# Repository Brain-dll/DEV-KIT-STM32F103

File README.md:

# dev_kit_f103
The project will be developed for designing new usable development kit with ARM cortex -M3 based STM32F103C8

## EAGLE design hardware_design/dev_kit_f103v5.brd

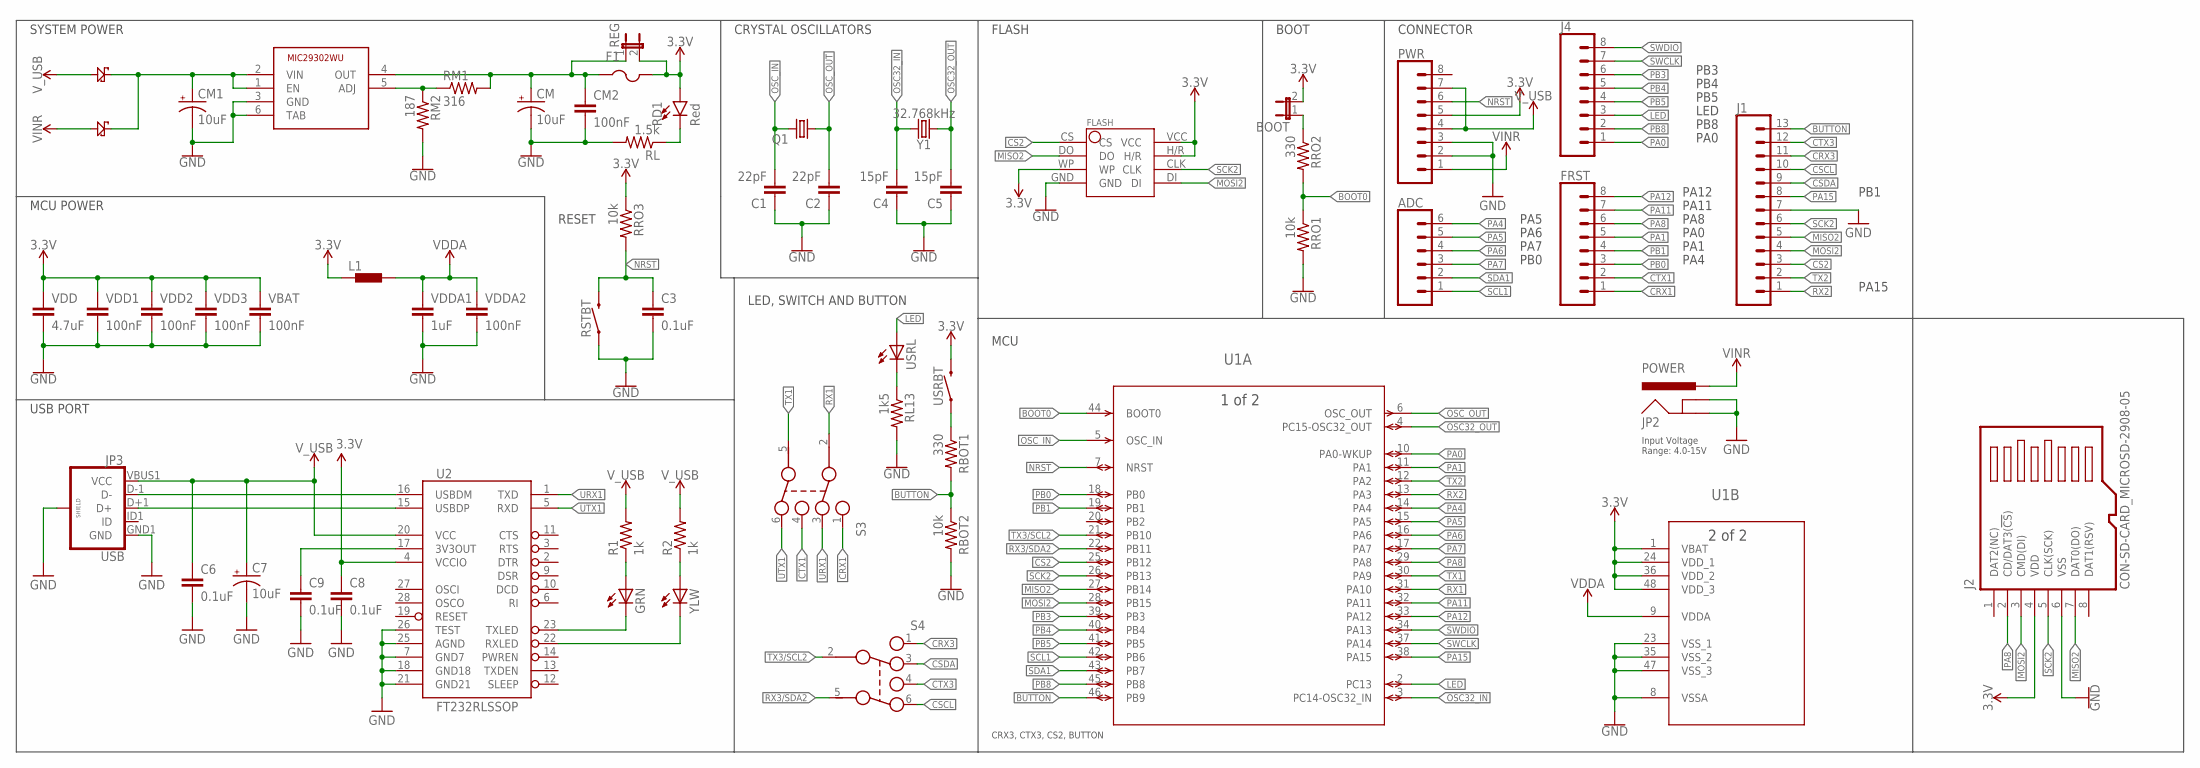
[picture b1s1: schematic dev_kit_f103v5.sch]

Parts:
ADC: CONN_06SILK_FEMALE_PTH; 1X06
BOOT: JP1E; JP1
C1, C2: 22pF; 0603
C3: 0.1uF; 0603
C4, C5: 15pF; 0603
C6, C8, C9: 0.1uF; 0402-CAP
C7: 10uF; EIA3216
CM, CM1: 10uF; EIA3528
CM2: 100nF; 0603
D1, D2: 3ASCHOOTKY
F1: PTCFUSE-1812; 1812
FLASH: W25Q64
FRST: CONN_08"; 1X08
GRN: LEDCHIP-LED0603; CHIP-LED0603
IC1: MIC29302WU; TO263-5
J1: CONN_13; 1X13
J2: CON-SD-CARD_MICROSD-2908-05; CON-SD-CARD_2908-05
J4: CONN_08"; 1X08
JP2: POWER; POWER_JACK_PTH_LOCK
JP3: USB; USB-B-MICRO-SMD_V03
L1: BLM15HB221SN1; 0402
PWR: CONN_08"; 1X08
Q1: CRYSTALHC49S; HC49/S
R1, R2: 1k; 0402-RES
RBOT1: 330; 0603-RES
RBOT2: 10k; 0603-RES
RD1: Red; LED-0603
REG: JP1E; JP1
RL: 1.5k; 0603-RES
RL13: 1k5; 0603-RES
RM1: 316; 0603-RES
RM2: 187; 0603-RES
RRO1, RRO3: 10k; 0603-RES
RRO2: 330; 0603-RES
RSTBT: MOMENTARY-SWITCH-SPST-SMD-6.0X3.5MM; TACTILE_SWITCH_SMD_6.0X3.5MM
S3, S4: 452403012014
U1: STM32F103C8T6; LQFP48-7X7MM
U2: FT232RLSSOP; SSOP28DB
USRBT: MOMENTARY-SWITCH-SPST-SMD-6.0X3.5MM; TACTILE_SWITCH_SMD_6.0X3.5MM
USRL: LEDCHIP-LED0603; CHIP-LED0603
VBAT: 100nF; 0603
VDD: 4.7uF; 0603
VDD1, VDD2, VDD3: 100nF; 0603
VDDA1: 1uF; 0603
VDDA2: 100nF; 0603
Y1: 32.768kHz; CRYSTAL-PTH-2X6-CYL-KIT
YLW: LEDCHIP-LED0603; CHIP-LED0603

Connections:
3.3V: BOOT.2, F1.2, FLASH.H/R, FLASH.VCC, FLASH.WP, J2.4 (VDD), L1.1, PWR.5, RD1.A, REG.2, RRO3.1, U1.1 (VBAT), U1.24 (VDD_1), U1.36 (VDD_2), U1.48 (VDD_3), USRBT.2, VBAT.1, VDD.1, VDD1.1, VDD2.1, VDD3.1
BOOT0: RRO1.1, RRO2.2, U1.44 (BOOT0)
BUTTON: J1.13, RBOT1.2, RBOT2.1, U1.46 (PB9)
CRX1: FRST.1, S3.1
CRX3: J1.11, S4.1
CS2: FLASH.CS, J1.3, U1.25 (PB12)
CSCL: J1.10, S4.6
CSDA: J1.9, S4.3
CTX1: FRST.2, S3.4
CTX3: J1.12, S4.4
GND: C1.1, C2.1, C3.2, C4.1, C5.1, C6.2, C7.C (-), C8.2, C9.2, CM.C (-), CM1.C (-), CM2.2, FLASH.GND, IC1.3 (GND), IC1.6 (TAB), J1.7, J2.6 (VSS), JP2.GND, JP2.GNDBREAK, JP3.GND1 (GND), JP3.SHIELD1 (SHIELD), JP3.SHIELD2 (SHIELD), JP3.SHIELD3 (SHIELD), PWR.2, PWR.3, RBOT2.2, RL.2, RL13.2, RM2.2, RRO1.2, RSTBT.1, U1.8 (VSSA), U1.23 (VSS_1), U1.35 (VSS_2), U1.47 (VSS_3), U2.7 (GND7), U2.18 (GND18), U2.21 (GND21), U2.25 (AGND), U2.26 (TEST), VBAT.2, VDD.2, VDD1.2, VDD2.2, VDD3.2, VDDA1.2, VDDA2.2
LED: J4.3, U1.2 (PC13), USRL.A
MISO2: FLASH.DO, J1.5, J2.7 (DAT0(DO)), U1.27 (PB14)
MOSI2: FLASH.DI, J1.4, J2.3 (CMD(DI)), U1.28 (PB15)
unnamed: CM1.A (+), D1.OUT, D2.OUT, IC1.1 (EN), IC1.2 (VIN)
unnamed: CM.A (+), CM2.1, F1.1, IC1.4 (OUT), REG.1, RM1.2
unnamed: BOOT.1, RRO2.1
unnamed: RL13.1, USRL.C
unnamed: RBOT1.1, USRBT.1
unnamed: GRN.A, R1.1
unnamed: R2.1, YLW.A
unnamed: C9.1, U2.17 (3V3OUT)
unnamed: IC1.5 (ADJ), RM1.1, RM2.1
unnamed: RD1.C, RL.1
NRST: C3.1, PWR.6, RRO3.2, RSTBT.2, U1.7 (NRST)
OSC32_IN: C4.2, U1.3 (PC14-OSC32_IN), Y1.2
OSC32_OUT: C5.2, U1.4 (PC15-OSC32_OUT), Y1.1
OSC_IN: C1.2, Q1.2, U1.5 (OSC_IN)
OSC_OUT: C2.2, Q1.1, U1.6 (OSC_OUT)
PA0: J4.1, U1.10 (PA0-WKUP)
PA1: FRST.5, U1.11 (PA1)
PA4: ADC.6, U1.14 (PA4)
PA5: ADC.5, U1.15 (PA5)
PA6: ADC.4, U1.16 (PA6)
PA7: ADC.3, U1.17 (PA7)
PA8: FRST.6, J2.2 (CD/DAT3(!CS!)), U1.29 (PA8)
PA11: FRST.7, U1.32 (PA11)
PA12: FRST.8, U1.33 (PA12)
PA15: J1.8, U1.38 (PA15)
PB0: FRST.3, U1.18 (PB0)
PB1: FRST.4, U1.19 (PB1)
PB3: J4.6, U1.39 (PB3)
PB4: J4.5, U1.40 (PB4)
PB5: J4.4, U1.41 (PB5)
PB8: J4.2, U1.45 (PB8)
RX1: S3.2, U1.31 (PA10)
RX2: J1.1, U1.13 (PA3)
RX3/SDA2: S4.5, U1.22 (PB11)
RXLED: U2.22 (RXLED), YLW.C
SCK2: FLASH.CLK, J1.6, J2.5 (CLK(SCK)), U1.26 (PB13)
SCL1: ADC.1, U1.42 (PB6)
SDA1: ADC.2, U1.43 (PB7)
SWCLK: J4.7, U1.37 (PA14)
SWDIO: J4.8, U1.34 (PA13)
TX1: S3.5, U1.30 (PA9)
TX2: J1.2, U1.12 (PA2)
TX3/SCL2: S4.2, U1.21 (PB10)
TXLED: GRN.C, U2.23 (TXLED)
URX1: S3.3, U2.1 (TXD)
USB_D+: JP3.D+1 (D+), U2.15 (USBDP)
USB_D-: JP3.D-1 (D-), U2.16 (USBDM)
UTX1: S3.6, U2.5 (RXD)
VCC: C8.1, U2.4 (VCCIO)
VDDA: L1.2, U1.9 (VDDA), VDDA1.1, VDDA2.1
VIN: D2.IN, JP2.PWR, PWR.1
V_USB: C6.1, C7.A (+), D1.IN, JP3.VBUS1 (VCC), PWR.4, PWR.7, R1.2, R2.2, U2.20 (VCC)

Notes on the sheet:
Input Voltage Range: 4.0-15V
SYSTEM POWER
MCU POWER
CRYSTAL OSCILLATORS
USB PORT
RESET
LED, SWITCH AND BUTTON
MCU
FLASH
BOOT
CONNECTOR
PA5
PA6
PA7
PB0
PA4
PA1
PA0
PA8
PA11
PA12
PA15
PB1
PB8
LED
PB5
PB4
PB3
CRX3, CTX3, CS2, BUTTON

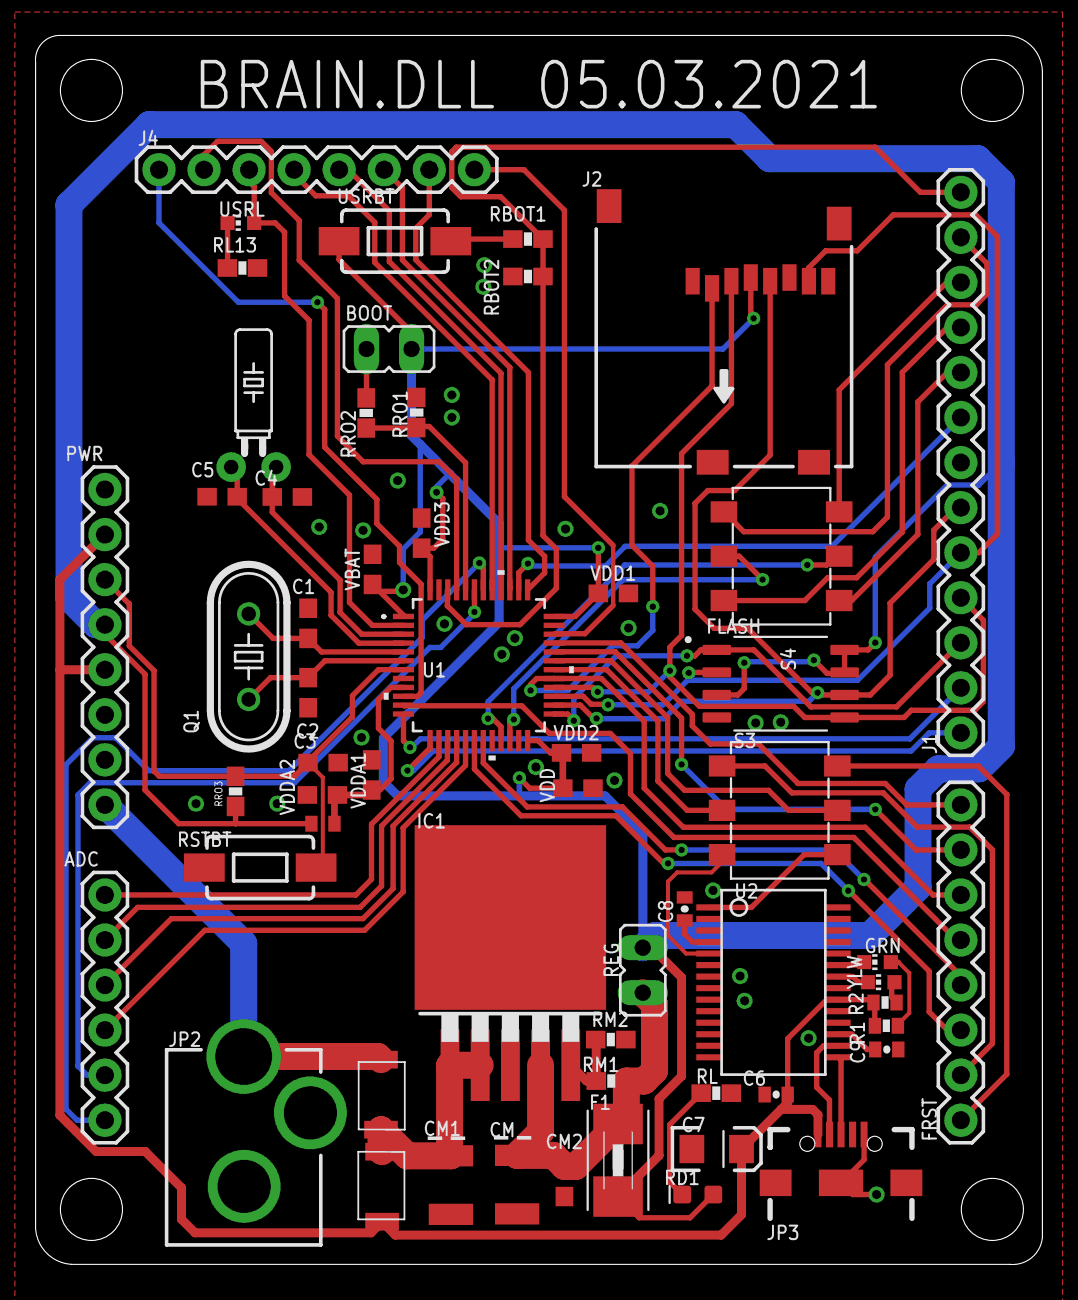
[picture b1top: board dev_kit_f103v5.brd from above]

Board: 2 copper layers, 56.8 x 69.3 mm, 58 parts (0 on the bottom side), 66 nets.

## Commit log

2021-02-26 Project was startted
2021-03-04 Version 2 was started to design
2021-03-04 Design was completed %40
2021-03-05 Hardware design v4 was completed, it is waiting for checking
2021-03-06 Drill size was changed (20 mil)
2021-03-10 Routes were be modified
2021-03-10 Bypass capacitors were located more close through to controller
2021-04-03 Polygon witdh was increased IMPORTANT**

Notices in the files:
parts and their libraries:
SparkFun-Connectors: Licensing: Creative Commons ShareAlike 4.0 International - https://creativecommons.org/licenses/by-sa/4.0
SparkFun-Resistors: Licensing: CC v3.0 Share-Alike You are welcome to use this library for commercial purposes.
step_switch: Copyright: Würth Elektronik
